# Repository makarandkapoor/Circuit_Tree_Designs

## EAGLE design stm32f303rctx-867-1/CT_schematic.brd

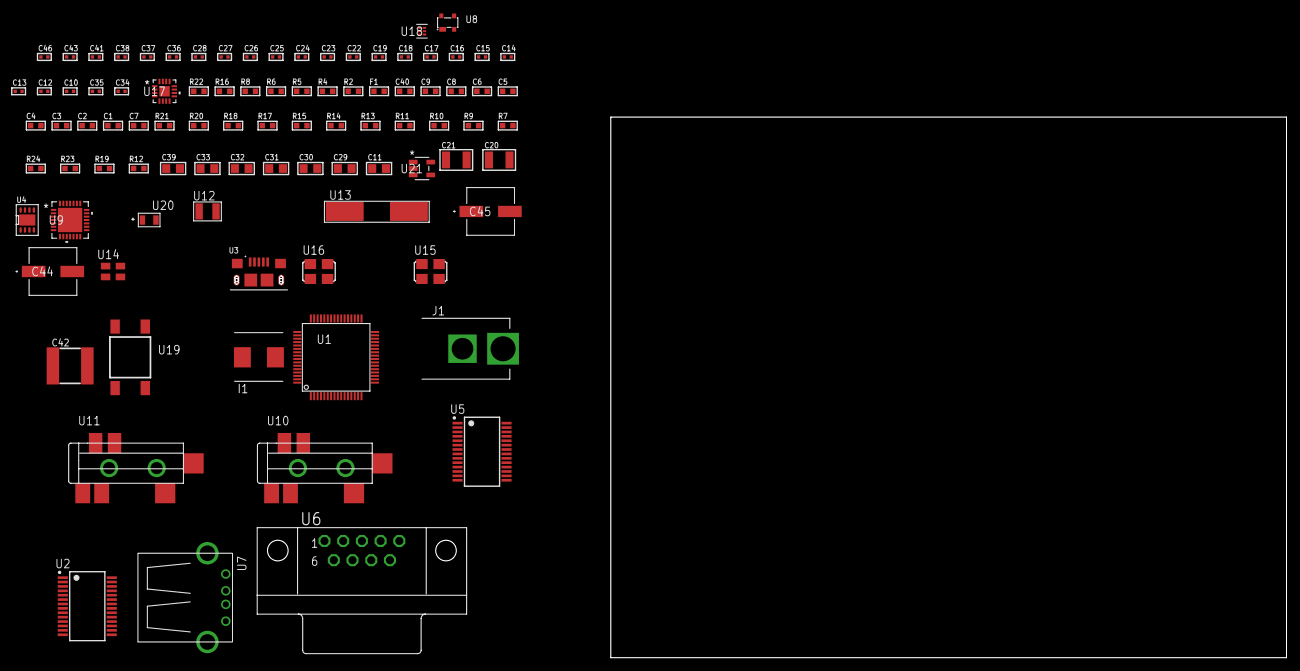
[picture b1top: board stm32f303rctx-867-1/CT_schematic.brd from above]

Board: 2 copper layers, 92 parts (0 on the bottom side), 59 nets, no tracks yet.

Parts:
C1, C9, C40: 1e-06; C0603
C2, C3, C4, C5, C6: 1e-07; C0603
C7: 4.7e-06; C0603
C8: 1e-08; C0603
C10, C12, C13, C14, C15, C16, C17, C18, C19, C24, C25, C26, C27, C28, C41, C43: 1e-07; C0402
C11: 4.7e-06; C0805
C20, C21: 2.2e-05; C1210
C22, C23: 1e-09; C0402
C29, C30, C31, C32, C33, C39: 1e-05; C0805
C34, C35: 2.2e-11; C0402
C36, C37, C38, C46: 1e-08; C0402
C42: 6.8e-05; 2220
C44, C45: 0.0001; EXV-9H
F1: 240.0; L0603
I1: 3.3e-06; WE-HCI_7030/7040/7050
J1: PJ-037B; PJ-037B_PACKAGE
R2: 1000.0; R0603
R4, R8: 4700.0; R0603
R5, R6: 2200.0; R0603
R7, R9, R10, R11, R20, R21: 10000.0; R0603
R12: 100000.0; R0603
R13, R14, R15: 47000.0; R0603
R16: 680.0; R0603
R17: 20000.0; R0603
R18: 91000.0; R0603
R19: 300000.0; R0603
R22: 9100.0; R0603
R23: 680000.0; R0603
R24: 120000.0; R0603
U1: STM32F303RCT6; LQFP64
U2: FT232RL-REEL; SSOP-28
U3: 10118193-0001LF; FCI_10118193-0001LF
U4: PCF85063TP/1Z; SON-8
U5: ST3241EBPR; SSOP-28
U6: 182-009-113R531; 182-009-MALE
U7: 61400416021; USB-A-H
U8: prtr5v0u2ax; SOT143B
U9: WM8731CLSEFL; QFN-28
U10, U11: SJ-43515TS-SMT-TR
U12: ABS07-32.768KHZ-7-T
U13: ABLS-12.288MHZ-B4-T
U14: ASEK-32.768KHz-ECST; ASEK
U15: ASFL1-12MHZ-NCS; ASFL1
U16: ASFL1-25MHZ-NCS; ASFL1
U17: LTC3601EUD#PBF; QFN-16_EP
U18: TPS3895ADRYR; SON-6
U19: 4-1437565-2; SW_4-1437565-2
U20: Q65110A2395; LGM67K-G1J2-24-Z
U21: nc7sz125m5x; NC7SZ125M5X

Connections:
CLK_CRYSTAL_U4_1: U4.1, U12.1
CLK_CRYSTAL_U4_2: U4.2, U12.2
CLK_CRYSTAL_U9_1: C34.1, U9.1, U13.1
CLK_CRYSTAL_U9_2: C35.1, U9.2, U13.2
CLK_U1_3: U1.3, U14.3
CLK_U1_5: U1.5, U16.3
CLK_U2_27: U2.27, U15.3
GND: C1.2, C2.2, C3.2, C4.2, C5.2, C6.2, C7.2, C8.2, C9.2, C10.2, C11.2, C12.2, C13.2, C14.2, C15.2, C18.2, C19.2, C23.2, C24.2, C25.2, C26.2, C27.2, C28.2, C29.2, C30.2, C31.2, C32.2, C33.2, C34.2, C35.2, C36.2, C37.2, C38.2, C39.2, C40.2, C42.1, C42.2, C43.2, C44.2, C45.2, C46.2, J1.2, R2.2, R7.2, R10.2, R13.2, R14.2, R15.2, R17.2, R19.2, R22.2, R24.2, U1.12, U1.31, U1.47, U1.63, U2.7, U2.18, U2.21, U2.25, U2.26, U3.5, U3.6, U3.7, U3.8, U3.9, U4.4, U4.PAD, U5.23, U5.25, U6.5, U7.4, U7.5, U7.6, U8.1, U9.4, U9.15, U9.19, U9.25, U9.26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
NET_U1_7: R4.1, U1.7, U21.4
NET_U1_13: C8.1, C9.1, F1.1, U1.13
NET_U1_49: R6.1, U1.49, U4.5
NET_U1_50: R5.1, U1.50, U4.6
NET_U1_60: R7.1, U1.60
NET_U1_62: U19.3, U19.4
NET_U2_14: R9.1, U2.14
NET_U2_17: C12.1, U2.17
NET_U2_19: R10.1, U2.19
NET_U3_1: R8.1, U3.1
NET_U3_2: U2.16, U3.2
NET_U3_3: U2.15, U3.3
NET_U4_3: R11.1, U4.3
NET_U5_1: C17.1, U5.1
NET_U5_2: C17.2, U5.2
NET_U5_3: C19.1, U5.3
NET_U5_22: R12.1, U5.22
NET_U5_24: C16.2, U5.24
NET_U5_27: C18.1, U5.27
NET_U5_28: C16.1, U5.28
NET_U6_2: U5.4, U6.2
NET_U6_3: U5.9, U6.3
NET_U6_7: U5.5, U6.7
NET_U6_8: U5.10, U6.8
NET_U8_4: U7.1, U8.4
NET_U9_20: C28.1, C33.1, U9.20
NET_U10_2: C21.1, R14.1, U10.2
NET_U10_5: C20.1, R13.1, U10.5
NET_U11_5: C22.1, C23.1, R15.1, R16.1, U11.5
NET_U17_3: C41.2, I1.1, U17.3, U17.4
NET_U17_6: C41.1, U17.6
NET_U17_7: C40.1, U17.7, U17.12
NET_U17_10: R19.1, U17.10
NET_U17_11: R17.1, R18.1, U17.11
NET_U17_ATNET_3: I1.2, R18.2
NET_U18_1: R21.1, R22.1, U18.1
NET_U18_3: R23.2, R24.1, U18.3
NET_U18_4: R20.1, U18.4, U21.2
NET_U19_1: R2.1, U19.1, U19.2
PROC_I2S2_CK: U1.34, U9.7
PROC_I2S2_EXT_SD: U1.35, U9.10
PROC_I2S2_SD: U1.36, U9.8
PROC_I2S2_WS: U1.33, U9.9, U9.11
PROC_UART4_RX: U1.52, U2.1
PROC_UART4_TX: U1.51, U2.5
PROC_UART5_RX: U1.54, U5.19
PROC_UART5_TX: U1.53, U5.14
PROC_USB_DM: U1.44, U7.2, U8.3
PROC_USB_DP: U1.45, U7.3, U8.2
VCC_S1_4V9: C39.1, C44.1, C45.1, J1.1, U17.15, U17.16
VCC_TIER1_3V3: C1.1, C2.1, C3.1, C4.1, C5.1, C6.1, C7.1, C10.1, C11.1, C13.1, C14.1, C15.1, C24.1, C25.1, C26.1, C27.1, C29.1, C30.1, C31.1, C32.1, C36.1, C37.1, C38.1, C42.2, C43.1, C46.1, F1.2, I1.2, R4.2, R5.2, R6.2, R9.2, R11.2, R12.2, R18.2, R20.2, R21.2, R23.1, U1.1, U1.19, U1.32, U1.48, U1.64, U2.4, U2.20, U4.8, U5.26, U9.3, U9.5, U9.12, U9.18, U14.4, U15.4, U16.4, U17.8, U18.6, U21.5

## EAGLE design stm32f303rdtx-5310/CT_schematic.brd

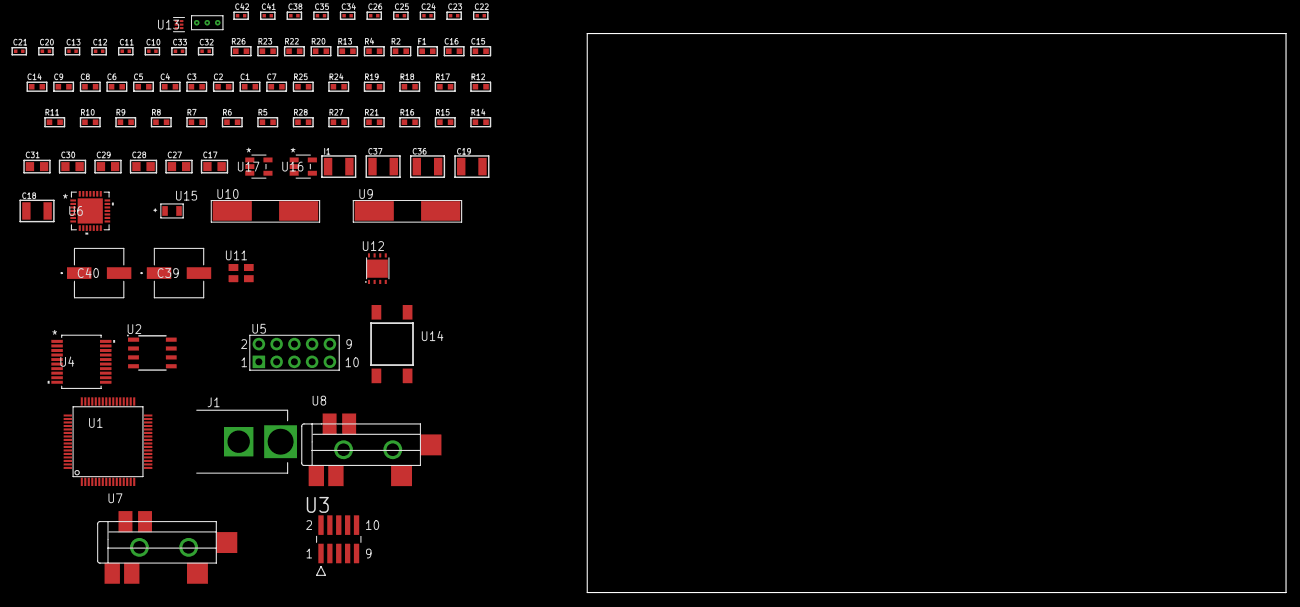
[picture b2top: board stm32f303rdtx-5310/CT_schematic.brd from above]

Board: 2 copper layers, 100.0 x 80.0 mm, 89 parts (0 on the bottom side), 55 nets, no tracks yet.

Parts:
C1, C9, C14, C15, C16: 1e-06; C0603
C2, C3, C4, C5, C6: 1e-07; C0603
C7: 4.7e-06; C0603
C8: 1e-08; C0603
C10, C11: 1e-11; C0402
C12, C34, C35, C41, C42: 1e-08; C0402
C13, C22, C23, C24, C25, C26, C38: 1e-07; C0402
C17: 4.7e-06; C0805
C18, C19: 2.2e-05; C1210
C20, C21: 1e-09; C0402
C27, C28, C29, C30, C31: 1e-05; C0805
C32, C33: 2.2e-11; C0402
C36, C37: 1e-05; C1210
C39, C40: 0.0001; EXV-9H
F1: 240.0; L0603
I1: 1.5e-05; L1210
J1: PJ-037B; PJ-037B_PACKAGE
R2, R23: 1000.0; R0603
R4: 4700.0; R0603
R5, R6, R7, R8, R9, R10, R11, R12, R24, R25: 10000.0; R0603
R13: 5.0; R0603
R14, R15, R16, R21: 100000.0; R0603
R17, R18, R19: 47000.0; R0603
R20: 680.0; R0603
R22: 2231.0; R0603
R26: 9100.0; R0603
R27: 680000.0; R0603
R28: 120000.0; R0603
U1: STM32F303RDT6; LQFP64
U2: AT25010B-SSHL-T; SOIC-8
U3: FTSH-105-01-L-DV-K; SAMTEC_FTSH-105-01-L-DV-K
U4: MAX3218EAP+T; SSOP-20
U5: HTSS-105-01-G-D
U6: WM8731CLSEFL; QFN-28
U7, U8: SJ-43515TS-SMT-TR
U9: ABLS-25.000MHZ-B2F-T
U10: ABLS-12.288MHZ-B4-T
U11: ASEK-32.768KHz-ECST; ASEK
U12: LP3878SDX-ADJ/NOPB; WSON-8
U13: TPS3895ADRYR; SON-6
U14: 4-1437565-2; SW_4-1437565-2
U15: Q65110A2395; LGM67K-G1J2-24-Z
U16, U17: nc7sz125m5x; NC7SZ125M5X
U18: Dummy; DUMMY_PACKAGE_186

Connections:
CLK_CRYSTAL_U1_5: C10.1, U1.5, U9.1
CLK_CRYSTAL_U1_6: C11.1, U1.6, U9.2
CLK_CRYSTAL_U6_1: C32.1, U6.1, U10.1
CLK_CRYSTAL_U6_2: C33.1, U6.2, U10.2
CLK_U1_3: U1.3, U11.3
GND: C1.2, C2.2, C3.2, C4.2, C5.2, C6.2, C7.2, C8.2, C9.2, C10.2, C11.2, C12.2, C13.2, C14.2, C15.2, C16.2, C21.2, C22.2, C23.2, C24.2, C25.2, C26.2, C27.2, C28.2, C29.2, C30.2, C31.2, C32.2, C33.2, C34.2, C35.2, C36.2, C37.2, C38.2, C39.2, C40.2, C41.2, C42.2, J1.2, R2.2, R5.2, R12.2, R13.2, R17.2, R18.2, R19.2, R23.2, R26.2, R28.2, U1.12, U1.18, U1.31, U1.47, U1.63, U2.4, U3.3, U3.5, U4.5, U4.17, U4.20, U5.9, U6.4, U6.15, U6.19, U6.25, U6.26, U6.29, U7.1, U8.1, U11.2, U12.3, U12.PAD, U13.2, U15.C, U16.2, U16.3, U17.1, U17.3, U18.1
NET_U1_7: R4.1, U1.7, U17.4
NET_U1_13: C8.1, C9.1, F1.1, U1.13
NET_U1_60: R5.1, U1.60
NET_U1_62: U14.3, U14.4
NET_U2_3: R6.1, U2.3
NET_U2_7: R8.1, U2.7
NET_U3_9: R13.1, U3.9
NET_U4_1: I1.1, U4.1
NET_U4_2: R14.1, U4.2
NET_U4_3: R15.1, U4.3
NET_U4_4: R16.1, U4.4
NET_U4_15: C16.1, U4.15
NET_U4_16: C17.2, U4.16
NET_U4_18: C17.1, U4.18
NET_U4_19: C15.1, U4.19
NET_U5_3: U4.12, U5.3
NET_U5_4: U4.11, U5.4
NET_U5_5: U4.14, U5.5
NET_U5_6: U4.13, U5.6
NET_U6_20: C26.1, C31.1, U6.20
NET_U7_2: C19.1, R18.1, U7.2
NET_U7_5: C18.1, R17.1, U7.5
NET_U8_5: C20.1, C21.1, R19.1, R20.1, U8.5
NET_U12_1: C35.1, U12.1
NET_U12_6: R22.2, R23.1, U12.6
NET_U12_8: R21.1, U12.8
NET_U13_1: R25.1, R26.1, U13.1
NET_U13_3: R27.2, R28.1, U13.3
NET_U13_4: R24.1, U13.4, U16.4, U17.2
NET_U14_1: R2.1, U14.1, U14.2
PROC_ADC1_IN1: U1.14, U18.3
PROC_ADC1_IN2: U1.15, U18.2
PROC_I2S2_CK: U1.34, U6.7
PROC_I2S2_EXT_SD: U1.35, U6.10
PROC_I2S2_SD: U1.36, U6.8
PROC_I2S2_WS: U1.33, U6.9, U6.11
PROC_SPI1_MISO: U1.22, U2.2
PROC_SPI1_MOSI: U1.23, U2.5
PROC_SPI1_NSS: R7.1, U1.20, U2.1
PROC_SPI1_SCK: U1.21, U2.6
PROC_SYS_JTCK_SWCLK: R12.1, U1.49, U3.4
PROC_SYS_JTDI: R10.1, U1.50, U3.8
PROC_SYS_JTDO_TRACESWO: U1.55, U3.6
PROC_SYS_JTMS_SWDIO: R11.1, U1.46, U3.2
PROC_UART4_RX: U1.52, U4.9
PROC_UART4_TX: U1.51, U4.7
RST_OUT_U3_JTAG_RST_B: R9.1, U3.10, U16.1
VCC_S1_15V0: C36.1, C39.1, C40.1, J1.1, R21.2, U12.4
VCC_TIER1_3V3: C1.1, C2.1, C3.1, C4.1, C5.1, C6.1, C7.1, C12.1, C13.1, C14.1, C22.1, C23.1, C24.1, C25.1, C27.1, C28.1, C29.1, C30.1, C34.1, C37.1, C38.1, C41.1, C42.1, F1.2, I1.2, R4.2, R6.2, R7.2, R8.2, R9.2, R10.2, R11.2, R14.2, R15.2, R16.2, R22.1, R24.2, R25.2, R27.1, U1.1, U1.19, U1.32, U1.48, U1.64, U2.8, U3.1, U4.6, U6.3, U6.5, U6.12, U6.18, U11.4, U12.5, U13.6, U16.5, U17.5

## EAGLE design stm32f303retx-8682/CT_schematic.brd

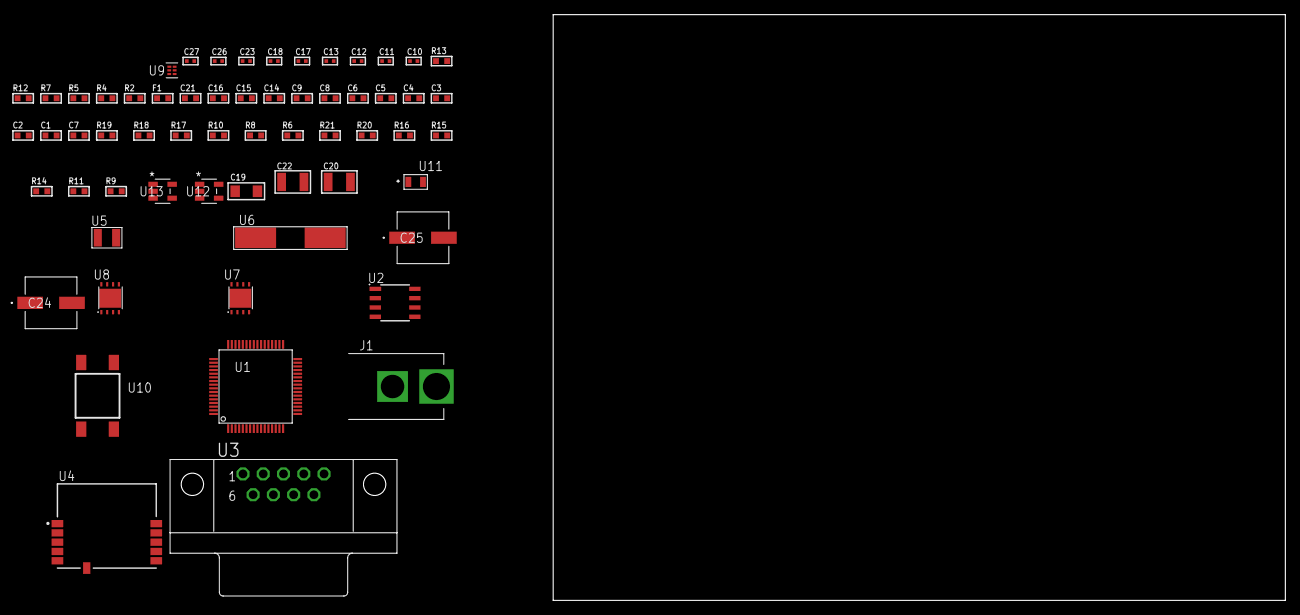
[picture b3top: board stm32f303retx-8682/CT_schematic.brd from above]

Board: 2 copper layers, 100.0 x 80.0 mm, 61 parts (0 on the bottom side), 32 nets, no tracks yet.

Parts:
C1, C9, C14, C15, C16, C21: 1e-06; C0603
C2, C3, C4, C5, C6: 1e-07; C0603
C7: 4.7e-06; C0603
C8: 1e-08; C0603
C10, C11, C12, C13: 1e-11; C0402
C17, C23: 1e-07; C0402
C18, C26, C27: 1e-08; C0402
C19: 1e-05; C1206
C20, C22: 1e-05; C1210
C24, C25: 0.0001; EXV-9H
F1: 240.0; L0603
J1: PJ-037B; PJ-037B_PACKAGE
R2, R13: 1000.0; R0603
R4, R5: 4700.0; R0603
R6, R8, R17, R18: 10000.0; R0603
R7: 120.0; R0603
R9, R11, R14, R16: 100000.0; R0603
R10: 47000.0; R0603
R12: 1500.0; R0603
R15: 300000.0; R0603
R19: 18000.0; R0603
R20: 470000.0; R0603
R21: 120000.0; R0603
U1: STM32F303RET7; LQFP64
U2: MCP2562-E/SN; SOIC-8
U3: 182-009-113R531; 182-009-MALE
U4: SPBTLE-RF; XCVR_SPBTLE-RF
U5: ABS07-32.768KHZ-7-T
U6: ABLS-25.000MHZ-B2F-T
U7: LP3878SDX-ADJ/NOPB; WSON-8
U8: LP2951ACSDX/NOPB; WSON-8
U9: TPS3895ADRYR; SON-6
U10: 4-1437565-2; SW_4-1437565-2
U11: Q65110A2395; LGM67K-G1J2-24-Z
U12, U13: nc7sz125m5x; NC7SZ125M5X

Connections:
CLK_CRYSTAL_U1_3: C10.1, U1.3, U5.1
CLK_CRYSTAL_U1_4: C11.1, U1.4, U5.2
CLK_CRYSTAL_U1_5: C12.1, U1.5, U6.1
CLK_CRYSTAL_U1_6: C13.1, U1.6, U6.2
GND: C1.2, C2.2, C3.2, C4.2, C5.2, C6.2, C7.2, C8.2, C9.2, C10.2, C11.2, C12.2, C13.2, C14.2, C15.2, C16.2, C17.2, C18.2, C19.2, C20.2, C21.2, C22.2, C23.2, C24.2, C25.2, C26.2, C27.2, J1.2, R2.2, R6.2, R9.2, R10.2, R13.2, R16.2, R19.2, R21.2, U1.12, U1.18, U1.31, U1.47, U1.63, U2.2, U2.8, U3.5, U4.6, U7.3, U7.PAD, U8.3, U8.4, U8.PAD, U9.2, U11.C, U12.1, U12.3, U13.1, U13.3
NET_U1_7: R5.1, U1.7, U13.4
NET_U1_13: C8.1, C9.1, F1.1, U1.13
NET_U1_60: R6.1, U1.60
NET_U1_62: U10.3, U10.4
NET_U2_6: R7.2, U2.6
NET_U3_2: R7.2, U2.6, U3.2
NET_U3_3: R7.1, U2.7, U3.3
NET_U4_11: R4.1, U4.11, U12.4
NET_U7_1: C18.1, U7.1
NET_U7_6: R12.2, R13.1, U7.6
NET_U7_8: R11.1, U7.8
NET_U8_5: R14.1, U8.5
NET_U8_7: R15.2, R16.1, U8.7
NET_U9_1: R18.1, R19.1, U9.1
NET_U9_3: R20.2, R21.1, U9.3
NET_U9_4: R17.1, U9.4, U12.2, U13.2
NET_U10_1: R2.1, U10.1, U10.2
PROC_CAN_RX: U1.44, U2.4
PROC_CAN_TX: U1.45, U2.1
PROC_GPIO_TO_U4_SPI_IRQ: R10.1, U1.2, U4.4
PROC_SPI1_MISO: U1.22, U4.8
PROC_SPI1_MOSI: U1.23, U4.9
PROC_SPI1_NSS: R8.1, U1.20, U4.10
PROC_SPI1_SCK: R9.1, U1.21, U4.7
VCC_S1_8V6: C19.1, C21.1, C24.1, C25.1, J1.1, R11.2, U7.4, U8.8
VCC_TIER1_2V5: C1.1, C2.1, C3.1, C4.1, C5.1, C6.1, C7.1, C15.1, C16.1, C17.1, C20.1, C23.1, C26.1, C27.1, F1.2, R4.2, R5.2, R8.2, R12.1, R17.2, R18.2, R20.1, U1.1, U1.19, U1.32, U1.48, U1.64, U2.5, U4.5, U7.5, U9.6, U12.5, U13.5
VCC_TIER1_5V0: C14.1, C22.1, R14.2, R15.1, U2.3, U8.1

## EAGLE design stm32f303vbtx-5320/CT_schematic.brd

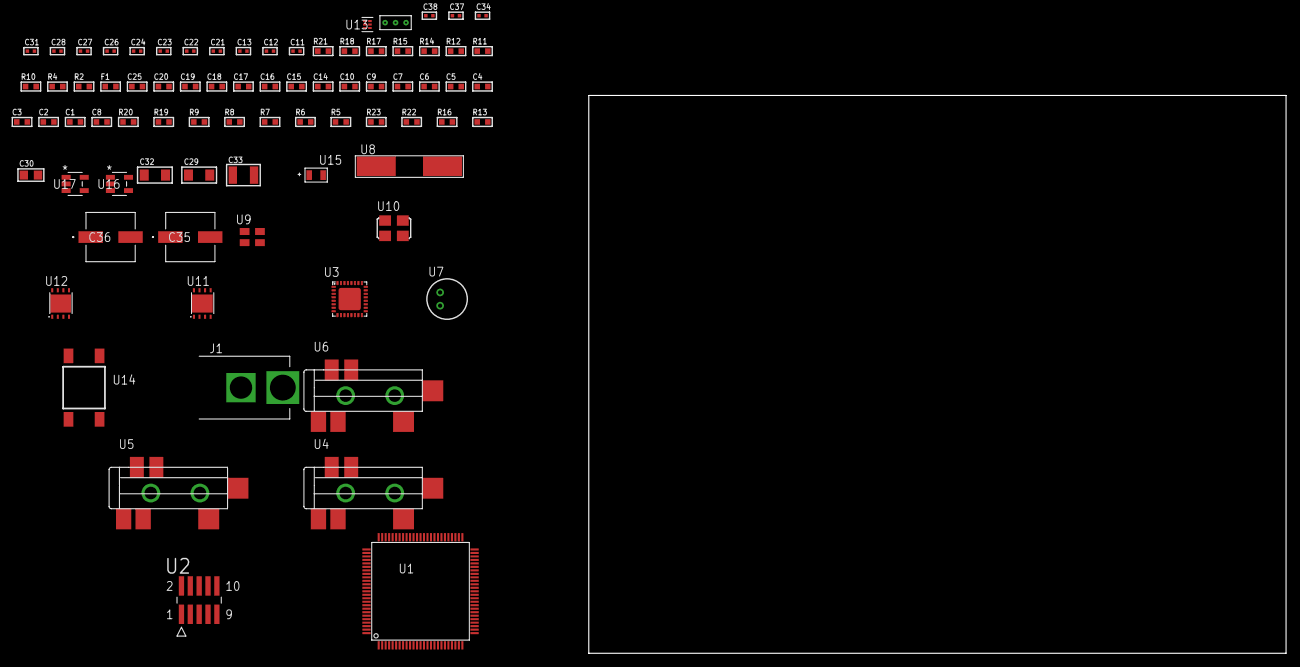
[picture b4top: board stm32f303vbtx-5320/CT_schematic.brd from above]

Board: 2 copper layers, 100.0 x 80.0 mm, 79 parts (0 on the bottom side), 47 nets, no tracks yet.

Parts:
C1, C10, C14, C15, C16, C17, C18, C19, C20, C25: 1e-06; C0603
C2, C3, C4, C5, C6, C7: 1e-07; C0603
C8: 4.7e-06; C0603
C9: 1e-08; C0603
C11, C12: 1e-11; C0402
C13, C21, C22, C23, C24, C34: 1e-07; C0402
C26, C27, C28, C31, C37, C38: 1e-08; C0402
C29, C32: 1e-05; C1206
C30: 1e-05; C0805
C33: 1e-05; C1210
C35, C36: 0.0001; EXV-9H
F1: 240.0; L0603
J1: PJ-037B; PJ-037B_PACKAGE
R2, R15, R18: 1000.0; R0603
R4: 4700.0; R0603
R5, R6, R7, R8, R9, R19, R20: 10000.0; R0603
R10: 5.0; R0603
R11, R12: 1270.0; R0603
R13, R16: 100000.0; R0603
R14: 200.0; R0603
R17: 2231.0; R0603
R21: 9100.0; R0603
R22: 680000.0; R0603
R23: 120000.0; R0603
U1: STM32F303VBT6; LQFP100
U2: FTSH-105-01-L-DV-K; SAMTEC_FTSH-105-01-L-DV-K
U3: SGTL5000XNAA3; QFN-32
U4, U5, U6: SJ-43515TS-SMT-TR
U7: WM-64PCT; WM-64PC
U8: ABLS-25.000MHZ-B2F-T
U9: ASEK-32.768KHz-ECST; ASEK
U10: ASFL-24.57MHZ-NCS; ASFL1
U11, U12: LP3878SDX-ADJ/NOPB; WSON-8
U13: TPS3895ADRYR; SON-6
U14: 4-1437565-2; SW_4-1437565-2
U15: Q65110A2395; LGM67K-G1J2-24-Z
U16, U17: nc7sz125m5x; NC7SZ125M5X
U18: Dummy; DUMMY_PACKAGE_164

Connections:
CLK_CRYSTAL_U1_12: C11.1, U1.12, U8.1
CLK_CRYSTAL_U1_13: C12.1, U1.13, U8.2
CLK_U1_8: U1.8, U9.3
CLK_U3_21: U3.21, U10.3
GND: C1.2, C2.2, C3.2, C4.2, C5.2, C6.2, C7.2, C8.2, C9.2, C10.2, C11.2, C12.2, C13.2, C21.2, C22.2, C23.2, C24.2, C25.2, C26.2, C27.2, C28.2, C29.2, C30.2, C31.2, C32.2, C33.2, C34.2, C35.2, C36.2, C37.2, C38.2, J1.2, R2.2, R5.2, R9.2, R10.2, R12.2, R15.2, R18.2, R21.2, R23.2, U1.20, U1.49, U1.74, U1.99, U2.3, U2.5, U3.1, U3.3, U3.7, U3.EXP, U5.1, U6.1, U7.2, U9.2, U10.2, U11.3, U11.PAD, U12.3, U12.PAD, U13.2, U15.C, U16.2, U16.3, U17.1, U17.3, U18.1
NET_U1_14: R4.1, U1.14, U17.4
NET_U1_22: C9.1, C10.1, F1.1, U1.21, U1.22
NET_U1_94: R5.1, U1.94
NET_U1_98: U14.3, U14.4
NET_U2_9: R10.1, U2.9
NET_U3_10: C24.1, U3.10
NET_U3_29: R11.1, U3.29
NET_U3_31: R12.1, U3.31
NET_U4_1: U3.4, U4.1
NET_U4_2: U3.2, U4.2
NET_U4_5: U3.6, U4.5
NET_U5_2: C15.1, U5.2
NET_U5_5: C14.1, U5.5
NET_U6_2: C17.1, C18.1, U6.2
NET_U6_5: C16.1, U6.5
NET_U6_13: C17.2, C18.2
NET_U7_1: C19.1, C20.1, C25.1, U3.16, U7.1
NET_U7_15: C19.2, C20.2
NET_U11_1: C28.1, U11.1
NET_U11_6: R14.2, R15.1, U11.6
NET_U11_8: R13.1, U11.8
NET_U12_1: C31.1, U12.1
NET_U12_6: R17.2, R18.1, U12.6
NET_U12_8: R16.1, U12.8
NET_U13_1: R20.1, R21.1, U13.1
NET_U13_3: R22.2, R23.1, U13.3
NET_U13_4: R19.1, U13.4, U16.4, U17.2
NET_U14_1: R2.1, U14.1, U14.2
PROC_I2S2_CK: U1.52, U3.24
PROC_I2S2_EXT_SD: U1.53, U3.25
PROC_I2S2_SD: U1.54, U3.26
PROC_I2S2_WS: U1.51, U3.23
PROC_PE2: U1.1, U18.2
PROC_PE3: U1.2, U18.3
PROC_SYS_JTCK_SWCLK: R9.1, U1.76, U2.4
PROC_SYS_JTDI: R7.1, U1.77, U2.8
PROC_SYS_JTDO_TRACESWO: U1.89, U2.6
PROC_SYS_JTMS_SWDIO: R8.1, U1.72, U2.2
RST_OUT_U2_JTAG_RST_B: R6.1, U2.10, U16.1
VCC_S1_5V3: C29.1, C32.1, C35.1, C36.1, J1.1, R13.2, R16.2, U11.4, U12.4
VCC_TIER1_1V2: C21.1, C30.1, R14.1, U3.30, U11.5
VCC_TIER1_3V3: C1.1, C2.1, C3.1, C4.1, C5.1, C6.1, C7.1, C8.1, C13.1, C22.1, C23.1, C26.1, C27.1, C33.1, C34.1, C37.1, C38.1, F1.2, R4.2, R6.2, R7.2, R8.2, R11.2, R17.1, R19.2, R20.2, R22.1, U1.6, U1.28, U1.50, U1.75, U1.100, U2.1, U3.5, U3.20, U9.4, U10.4, U12.5, U13.6, U16.5, U17.5

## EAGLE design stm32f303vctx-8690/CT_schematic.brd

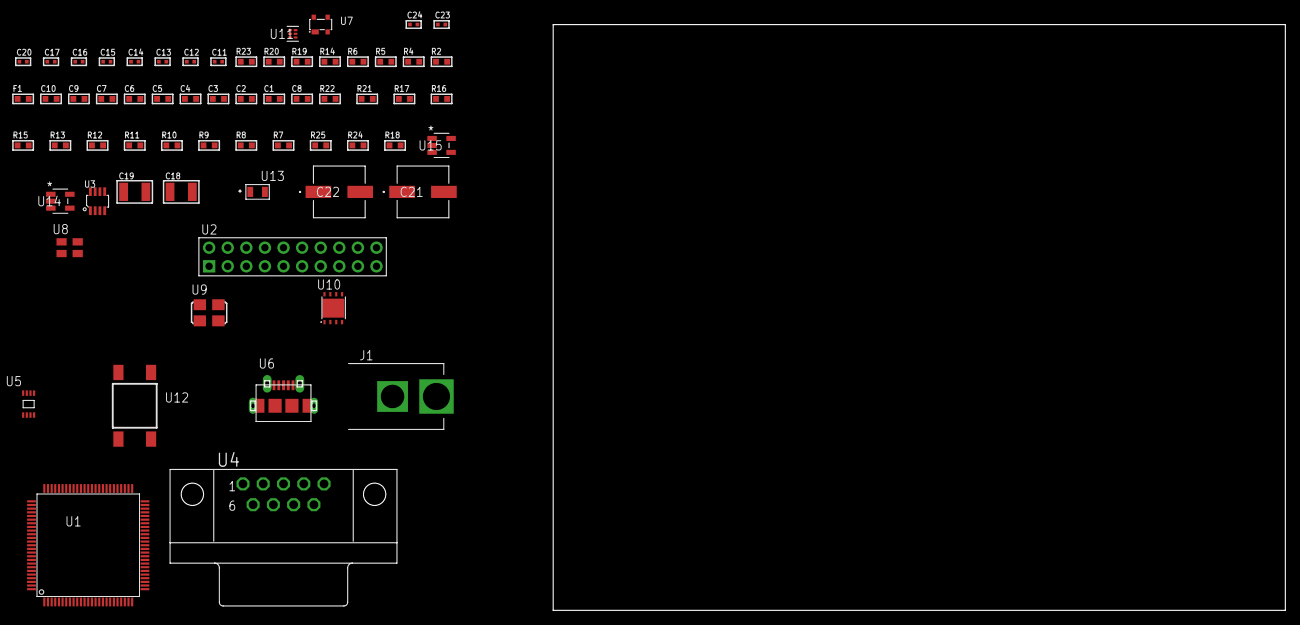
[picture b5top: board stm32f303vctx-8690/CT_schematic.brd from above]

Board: 2 copper layers, 64 parts (0 on the bottom side), 36 nets, no tracks yet.

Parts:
C1, C10: 1e-06; C0603
C2, C3, C4, C5, C6, C7: 1e-07; C0603
C8: 4.7e-06; C0603
C9: 1e-08; C0603
C11, C12, C13, C20: 1e-07; C0402
C14, C15, C16, C17, C23, C24: 1e-08; C0402
C18, C19: 1e-05; C1210
C21, C22: 0.0001; EXV-9H
F1: 240.0; L0603
J1: PJ-037B; PJ-037B_PACKAGE
R2, R20: 1000.0; R0603
R4: 4700.0; R0603
R5, R6: 2200.0; R0603
R7, R8, R9, R10, R11, R12, R13, R15, R16, R17, R21, R22: 10000.0; R0603
R14: 120.0; R0603
R18: 100000.0; R0603
R19: 2231.0; R0603
R23: 9100.0; R0603
R24: 680000.0; R0603
R25: 120000.0; R0603
U1: STM32F303VCT7; LQFP100
U2: TST-110-05-T-D-RA
U3: MAX3051EKA+T; SOT-23-8
U4: 182-009-113R531; 182-009-MALE
U5: 24AA64T-I/MNY; TDFN-8/6MM
U6: 47590-0001; MICRO_USB_AB
U7: prtr5v0u2ax; SOT143B
U8: ASEK-32.768KHz-ECST; ASEK
U9: ASFL1-25MHZ-NCS; ASFL1
U10: LP3878SDX-ADJ/NOPB; WSON-8
U11: TPS3895ADRYR; SON-6
U12: 4-1437565-2; SW_4-1437565-2
U13: Q65110A2395; LGM67K-G1J2-24-Z
U14, U15: nc7sz125m5x; NC7SZ125M5X

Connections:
CLK_U1_8: U1.8, U8.3
CLK_U1_12: U1.12, U9.3
GND: C1.2, C2.2, C3.2, C4.2, C5.2, C6.2, C7.2, C8.2, C9.2, C10.2, C11.2, C12.2, C13.2, C14.2, C15.2, C16.2, C17.2, C18.2, C19.2, C20.2, C21.2, C22.2, C23.2, C24.2, J1.2, R2.2, R7.2, R13.2, R16.2, R17.2, R20.2, R23.2, R25.2, U1.20, U1.49, U1.74, U1.99, U2.4, U2.6, U2.8, U2.10, U2.12, U2.14, U2.16, U2.18, U2.20, U3.2, U3.8, U4.5, U5.4, U5.7, U6.5, U6.6, U6.7, U6.8, U6.9, U7.1, U8.2, U9.2, U10.3, U10.PAD, U11.2, U13.C, U14.2, U14.3, U15.1, U15.3
NET_U1_14: R4.1, U1.14, U15.4
NET_U1_22: C9.1, C10.1, F1.1, U1.21, U1.22
NET_U1_92: R5.1, U1.92, U5.6
NET_U1_93: R6.1, U1.93, U5.5
NET_U1_94: R7.1, U1.94
NET_U1_98: U12.3, U12.4
NET_U2_19: R13.1, U2.19
NET_U3_6: R14.2, U3.6
NET_U4_2: R14.2, U3.6, U4.2
NET_U4_3: R14.1, U3.7, U4.3
NET_U5_1: R15.1, U5.1
NET_U5_2: R16.1, U5.2
NET_U5_3: R17.1, U5.3
NET_U7_4: U6.1, U7.4
NET_U10_1: C17.1, U10.1
NET_U10_6: R19.2, R20.1, U10.6
NET_U10_8: R18.1, U10.8
NET_U11_1: R22.1, R23.1, U11.1
NET_U11_3: R24.2, R25.1, U11.3
NET_U11_4: R21.1, U11.4, U14.4, U15.2
NET_U12_1: R2.1, U12.1, U12.2
PROC_CAN_RX: U1.81, U3.4
PROC_CAN_TX: U1.82, U3.1
PROC_SYS_JTCK_SWCLK: R11.1, U1.76, U2.9
PROC_SYS_JTDI: R9.1, U1.77, U2.5
PROC_SYS_JTDO_TRACESWO: U1.89, U2.13
PROC_SYS_JTMS_SWDIO: R10.1, U1.72, U2.7
PROC_SYS_NJTRST: R8.1, U1.90, U2.3
PROC_USB_DM: U1.70, U6.2, U7.3
PROC_USB_DP: U1.71, U6.3, U7.2
RST_OUT_U2_SRESET_B: R12.1, U2.15, U14.1
VCC_S1_12V1: C18.1, C21.1, C22.1, J1.1, R18.2, U10.4
VCC_TIER1_3V3: C1.1, C2.1, C3.1, C4.1, C5.1, C6.1, C7.1, C8.1, C11.1, C12.1, C13.1, C14.1, C15.1, C16.1, C19.1, C20.1, C23.1, C24.1, F1.2, R4.2, R5.2, R6.2, R8.2, R9.2, R10.2, R11.2, R12.2, R15.2, R19.1, R21.2, R22.2, R24.1, U1.6, U1.28, U1.50, U1.75, U1.100, U2.1, U2.2, U3.3, U5.8, U8.4, U9.4, U10.5, U11.6, U14.5, U15.5

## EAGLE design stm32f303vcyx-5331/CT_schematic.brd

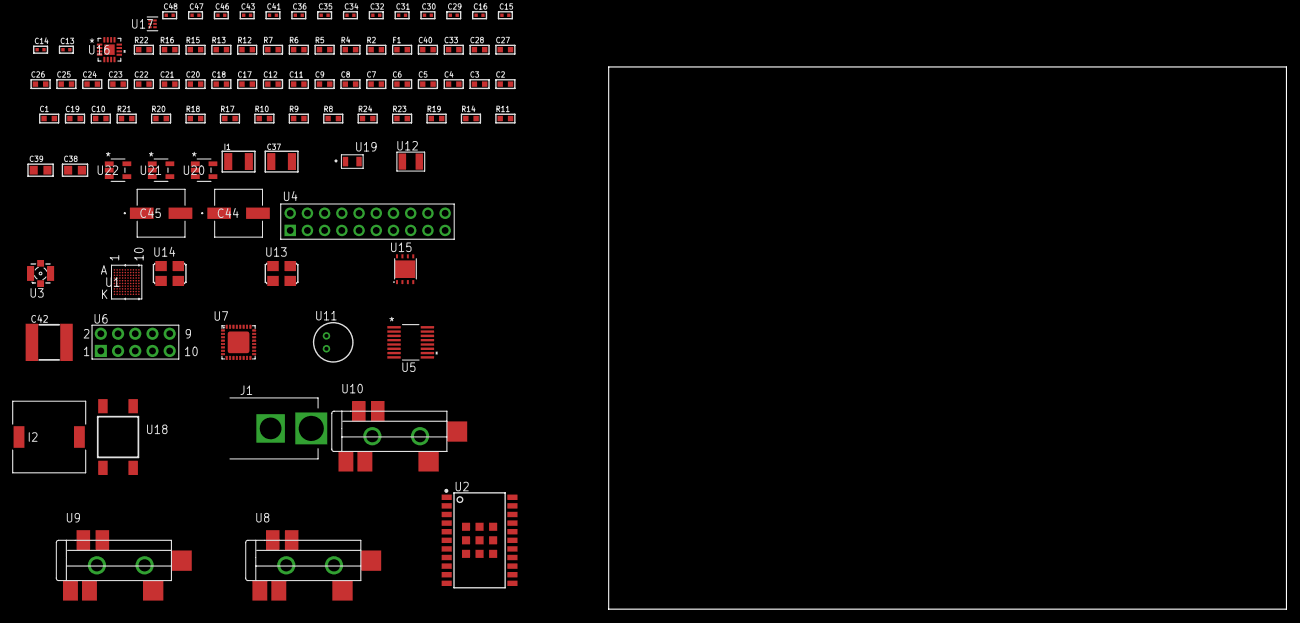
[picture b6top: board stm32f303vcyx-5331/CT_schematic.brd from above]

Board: 2 copper layers, 100.0 x 80.0 mm, 96 parts (0 on the bottom side), 64 nets, no tracks yet.

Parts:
C1, C12, C17, C18, C20, C21, C22, C23, C24, C25, C26, C27, C28, C33, C40: 1e-06; C0603
C2, C3, C4, C5, C6, C7, C8, C9: 1e-07; C0603
C10: 4.7e-06; C0603
C11: 1e-08; C0603
C13, C14: 1e-11; C0402
C15, C16, C29, C30, C31, C32, C41, C43: 1e-07; C0402
C19: 2.2e-07; C0603
C34, C35, C36, C46, C47, C48: 1e-08; C0402
C37: 1e-05; C1210
C38, C39: 1e-05; C0805
C42: 6.8e-05; 2220
C44, C45: 0.0001; EXV-9H
F1: 240.0; L0603
I1: 1e-05; L1210
I2: 7e-06; DR1040
J1: PJ-037B; PJ-037B_PACKAGE
R2, R16: 1000.0; R0603
R4, R5: 4700.0; R0603
R6, R7: 2200.0; R0603
R8, R9, R10, R20, R21: 10000.0; R0603
R11, R14: 100000.0; R0603
R12, R13: 1270.0; R0603
R15: 200.0; R0603
R17: 20000.0; R0603
R18: 91000.0; R0603
R19: 300000.0; R0603
R22: 9100.0; R0603
R23: 680000.0; R0603
R24: 120000.0; R0603
U1: STM32F303VCY6TR; WLCSP100
U2: A2200-A
U3: 73412-0114; COAXIAL_C
U4: TST-110-05-T-D-RA
U5: LTC2804CGN-1#PBF; SSOP-16
U6: HTSS-105-01-G-D
U7: SGTL5000XNAA3; QFN-32
U8, U9, U10: SJ-43515TS-SMT-TR
U11: WM-64PCT; WM-64PC
U12: ABS07-32.768KHZ-7-T
U13: ASFL-24.57MHZ-NCS; ASFL1
U14: ASFL1-25MHZ-NCS; ASFL1
U15: LP3878SDX-ADJ/NOPB; WSON-8
U16: LTC3601EUD#PBF; QFN-16_EP
U17: TPS3895ADRYR; SON-6
U18: 4-1437565-2; SW_4-1437565-2
U19: Q65110A2395; LGM67K-G1J2-24-Z
U20, U21, U22: nc7sz125m5x; NC7SZ125M5X

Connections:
CLK_CRYSTAL_U1_C10: C13.1, U1.C10, U12.1
CLK_CRYSTAL_U1_D9: C14.1, U1.D9, U12.2
CLK_U1_F10: U1.F10, U14.3
CLK_U7_21: U7.21, U13.3
GND: C1.2, C2.2, C3.2, C4.2, C5.2, C6.2, C7.2, C8.2, C9.2, C10.2, C11.2, C12.2, C13.2, C14.2, C15.2, C16.2, C17.2, C18.2, C20.2, C21.2, C29.2, C30.2, C31.2, C32.2, C33.2, C34.2, C35.2, C36.2, C37.2, C38.2, C39.2, C40.2, C42.1, C42.2, C43.2, C44.2, C45.2, C46.2, C47.2, C48.2, J1.2, R2.2, R8.2, R13.2, R16.2, R17.2, R19.2, R22.2, R24.2, U1.A1, U1.A2, U1.B1, U1.C7, U1.H8, U1.J1, U1.K1, U1.K2, U1.K9, U1.K10, U2.7, U2.8, U2.23, U2.24, U2.25, U2.26, U2.27, U2.28, U2.29, U2.30, U2.31, U4.4, U4.6, U4.8, U4.10, U4.12, U4.14, U4.16, U4.18, U4.20, U5.8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
NET_U1_A7: R8.1, U1.A7
NET_U1_B2: R6.1, U1.B2, U2.15
NET_U1_C5: R7.1, U1.C5, U2.16
NET_U1_E9: R5.1, U1.E9, U22.4
NET_U1_J10: C11.1, C12.1, F1.1, U1.J8, U1.J10
NET_U1_K7: U18.3, U18.4
NET_U2_2: R9.2, U2.2
NET_U2_17: R9.1, U2.17
NET_U2_22: R4.1, U2.22, U21.4
NET_U3_1: U2.11, U3.1
NET_U3_2: U2.10, U3.2, U3.3, U3.4
NET_U5_6: C17.1, U5.6
NET_U5_7: C19.1, I1.2, U5.7
NET_U5_9: C18.1, U5.9
NET_U5_10: C19.2, U5.10
NET_U5_11: R11.1, U5.11
NET_U6_3: U5.1, U6.3
NET_U6_4: U5.2, U6.4
NET_U6_5: U5.3, U6.5
NET_U6_6: U5.4, U6.6
NET_U7_10: C32.1, U7.10
NET_U7_29: R12.1, U7.29
NET_U7_31: R13.1, U7.31
NET_U8_1: U7.4, U8.1
NET_U8_2: U7.2, U8.2
NET_U8_5: U7.6, U8.5
NET_U9_2: C23.1, U9.2
NET_U9_5: C22.1, U9.5
NET_U10_2: C25.1, C26.1, U10.2
NET_U10_5: C24.1, U10.5
NET_U10_13: C25.2, C26.2
NET_U11_1: C27.1, C28.1, C33.1, U7.16, U11.1
NET_U11_15: C27.2, C28.2
NET_U15_1: C36.1, U15.1
NET_U15_6: R15.2, R16.1, U15.6
NET_U15_8: R14.1, U15.8
NET_U16_3: C41.2, I2.1, U16.3, U16.4
NET_U16_6: C41.1, U16.6
NET_U16_7: C40.1, U16.7, U16.12
NET_U16_10: R19.1, U16.10
NET_U16_11: R17.1, R18.1, U16.11
NET_U16_ATNET_3: I2.2, R18.2
NET_U17_1: R21.1, R22.1, U17.1
NET_U17_3: R23.2, R24.1, U17.3
NET_U17_4: R20.1, U17.4, U20.4, U21.2, U22.2
NET_U18_1: R2.1, U18.1, U18.2
PROC_I2S2_CK: U1.J3, U7.24
PROC_I2S2_EXT_SD: U1.J2, U7.25
PROC_I2S2_SD: U1.H4, U7.26
PROC_I2S2_WS: U1.J4, U7.23
PROC_SYS_JTCK_SWCLK: U1.C2, U4.9
PROC_SYS_JTDO_TRACESWO: U1.A5, U4.13
PROC_SYS_JTMS_SWDIO: U1.E3, U4.7
PROC_UART4_RX: U1.D3, U5.16
PROC_UART4_TX: U1.E4, U5.14
RST_OUT_U4_SRESET_B: R10.1, U4.15, U20.1
VCC_S1_12V5: C37.1, C39.1, C44.1, C45.1, J1.1, R14.2, U15.4, U16.15, U16.16
VCC_TIER1_1V2: C29.1, C38.1, R15.1, U7.30, U15.5
VCC_TIER1_3V3: C1.1, C2.1, C3.1, C4.1, C5.1, C6.1, C7.1, C8.1, C9.1, C10.1, C15.1, C16.1, C20.1, C21.1, C30.1, C31.1, C34.1, C35.1, C42.2, C43.1, C46.1, C47.1, C48.1, F1.2, I1.1, I2.2, R4.2, R5.2, R6.2, R7.2, R10.2, R11.2, R12.2, R18.2, R20.2, R21.2, R23.1, U1.A9, U1.A10, U1.B8, U1.B10, U1.D2, U1.D8, U1.J5, U1.K8, U2.20, U4.1, U5.5, U5.12, U7.5, U7.20, U13.4, U14.4, U16.8, U17.6, U20.5, U21.5, U22.5

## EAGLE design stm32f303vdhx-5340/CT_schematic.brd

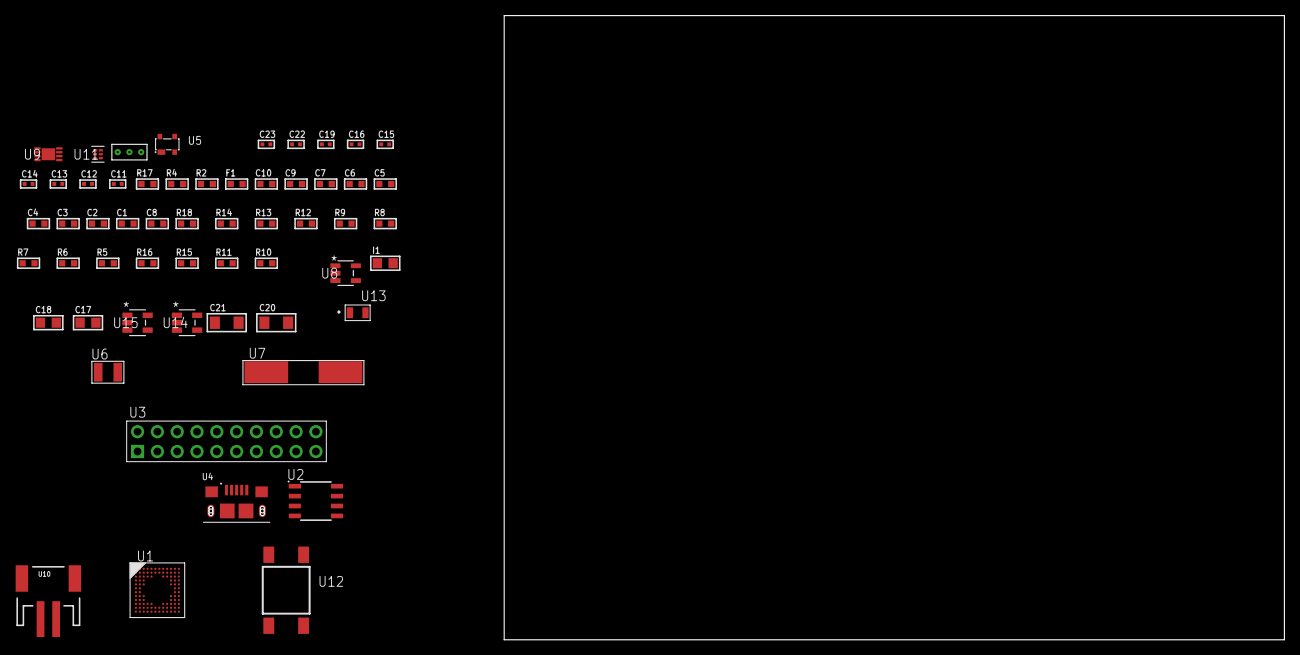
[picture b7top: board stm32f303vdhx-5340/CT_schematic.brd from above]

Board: 2 copper layers, 57 parts (0 on the bottom side), 35 nets, no tracks yet.

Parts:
C1, C10: 1e-06; C0603
C2, C3, C4, C5, C6, C7: 1e-07; C0603
C8: 4.7e-06; C0603
C9: 1e-08; C0603
C11, C12, C13, C14: 1e-11; C0402
C15, C22, C23: 1e-08; C0402
C16, C19: 1e-07; C0402
C17, C18: 1e-05; C0805
C20, C21: 1e-05; C1206
F1: 240.0; L0603
I1: 4.7e-06; L0805
R2: 1000.0; R0603
R4: 4700.0; R0603
R5, R6, R7, R8, R9, R12, R13, R18: 10000.0; R0603
R10: 309473.68421053; R0603
R11: 1000000.0; R0603
R14: 18000.0; R0603
R15: 470000.0; R0603
R16: 120000.0; R0603
R17: 2000.0; R0603
U1: STM32F303VDH6; UFBGA100
U2: AT25640B-SSHL-T; SOIC-8
U3: TST-110-05-T-D-RA
U4: 10118193-0001LF; FCI_10118193-0001LF
U5: prtr5v0u2ax; SOT143B
U6: ABS07-32.768KHZ-7-T
U7: ABLS-25.000MHZ-B2F-T
U8: ltc3406es5; TSOT-23-5
U9: MCP73831T-2ACI/MC; DFN8_2X3MC
U10: S2B-PH-SM4-TB(LF)(SN); JST-2-SMD
U11: TPS3895ADRYR; SON-6
U12: 4-1437565-2; SW_4-1437565-2
U13: Q65110A2395; LGM67K-G1J2-24-Z
U14, U15: nc7sz125m5x; NC7SZ125M5X
U16: Dummy; DUMMY_PACKAGE_122

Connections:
CLK_CRYSTAL_U1_D1: C11.1, U1.D1, U6.1
CLK_CRYSTAL_U1_E1: C12.1, U1.E1, U6.2
CLK_CRYSTAL_U1_F1: C13.1, U1.F1, U7.1
CLK_CRYSTAL_U1_G1: C14.1, U1.G1, U7.2
GND: C1.2, C2.2, C3.2, C4.2, C5.2, C6.2, C7.2, C8.2, C9.2, C10.2, C11.2, C12.2, C13.2, C14.2, C15.2, C16.2, C17.2, C18.1, C18.2, C19.2, C20.2, C21.2, C22.2, C23.2, R2.2, R5.2, R10.2, R14.2, R16.2, R17.2, U1.D3, U1.E3, U1.F11, U1.F12, U1.K1, U2.4, U3.4, U3.6, U3.8, U3.10, U3.12, U3.14, U3.16, U3.18, U3.20, U4.5, U4.6, U4.7, U4.8, U4.9, U5.1, U8.2, U9.6, U9.9, U10.2, U11.2, U13.C, U14.2, U14.3, U15.1, U15.3, U16.1
INPUT_USBPOWER_5V: C20.1, R18.2, U4.1, U5.4, U9.1, U9.2
NET_U1_A4: R5.1, U1.A4
NET_U1_H2: R4.1, U1.H2, U15.4
NET_U1_L1: C9.1, C10.1, F1.1, U1.L1, U1.M1
NET_U1_M12: U12.3, U12.4
NET_U2_3: R6.1, U2.3
NET_U2_7: R8.1, U2.7
NET_U8_3: I1.1, U8.3
NET_U8_5: R10.1, R11.1, U8.5
NET_U8_ATNET_3: I1.2, R11.2
NET_U9_5: R18.1, U9.5
NET_U9_8: R17.1, U9.8
NET_U11_1: R13.1, R14.1, U11.1
NET_U11_3: R15.2, R16.1, U11.3
NET_U11_4: R12.1, U11.4, U14.4, U15.2
NET_U12_1: R2.1, U12.1, U12.2
PROC_SPI1_MISO: U1.A7, U2.2
PROC_SPI1_MOSI: U1.C5, U2.5
PROC_SPI1_NSS: R7.1, U1.A9, U2.1
PROC_SPI1_SCK: U1.K4, U2.6
PROC_SYS_JTCK_SWCLK: U1.A10, U3.9
PROC_SYS_JTDO_TRACESWO: U1.A8, U3.13
PROC_SYS_JTMS_SWDIO: U1.A11, U3.7
PROC_TIM1_CH2: U1.D10, U16.2
PROC_TIM1_CH3: U1.C12, U16.3
PROC_USB_DM: U4.2, U5.3
PROC_USB_DP: U4.3, U5.2
RST_OUT_U3_SRESET_B: R9.1, U3.15, U14.1
VCC_S1_3V7: C17.1, C21.1, U8.4, U9.3, U9.4, U10.1
VCC_TIER1_2V5: C1.1, C2.1, C3.1, C4.1, C5.1, C6.1, C7.1, C8.1, C15.1, C16.1, C18.2, C19.1, C22.1, C23.1, F1.2, I1.2, R4.2, R6.2, R7.2, R8.2, R9.2, R11.2, R12.2, R13.2, R15.1, U1.C4, U1.E2, U1.G11, U1.G12, U1.H3, U2.8, U3.1, U11.6, U14.5, U15.5

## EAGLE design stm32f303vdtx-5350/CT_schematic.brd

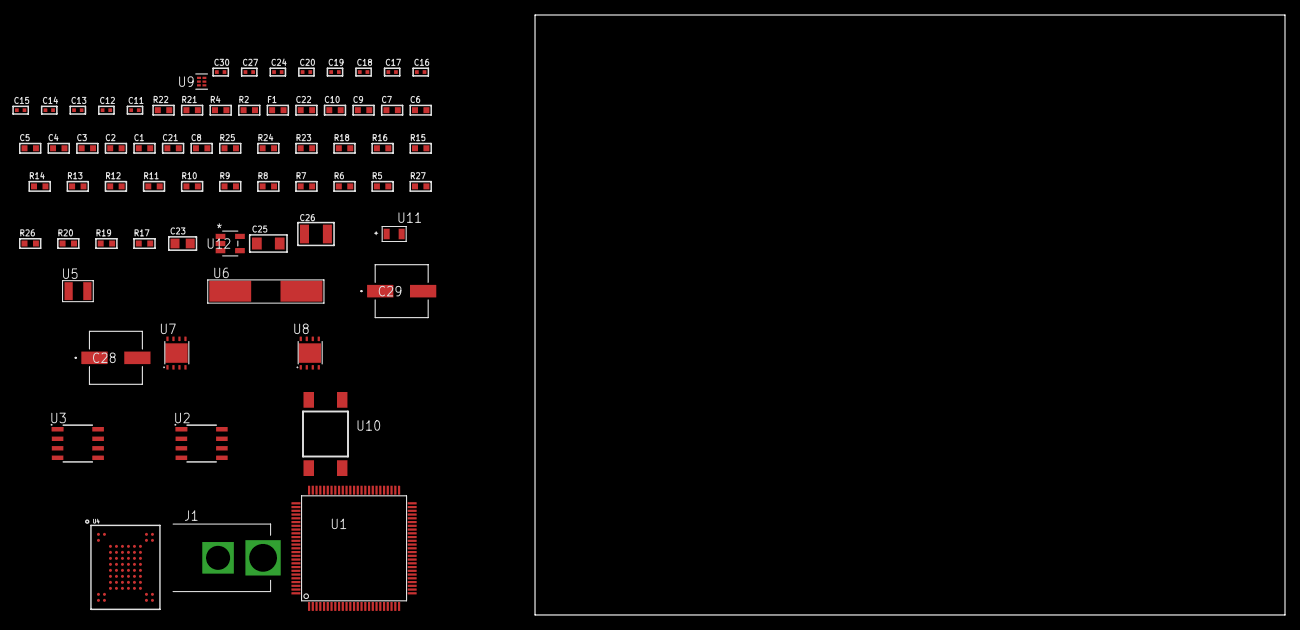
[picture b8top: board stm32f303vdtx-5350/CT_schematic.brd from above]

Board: 2 copper layers, 100.0 x 80.0 mm, 69 parts (0 on the bottom side), 38 nets, no tracks yet.

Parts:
C1, C10, C22: 1e-06; C0603
C2, C3, C4, C5, C6, C7: 1e-07; C0603
C8: 4.7e-06; C0603
C9: 1e-08; C0603
C11, C12, C13, C14: 1e-11; C0402
C15, C16, C24, C30: 1e-08; C0402
C17, C18, C19, C20, C27: 1e-07; C0402
C21: 2.2e-06; C0603
C23: 1e-05; C0805
C25: 1e-05; C1206
C26: 1e-05; C1210
C28, C29: 0.0001; EXV-9H
F1: 240.0; L0603
J1: PJ-037B; PJ-037B_PACKAGE
R2, R22: 1000.0; R0603
R4: 4700.0; R0603
R5, R6, R7, R8, R9, R10, R11, R12, R13, R14, R15, R16, R23, R24: 10000.0; R0603
R17, R19, R20: 100000.0; R0603
R18: 36000.0; R0603
R21: 1500.0; R0603
R25: 18000.0; R0603
R26: 470000.0; R0603
R27: 120000.0; R0603
U1: STM32F303VDT6; LQFP100
U2: AT25020B-SSHL-T; SOIC-8
U3: AT25160B-SSHL-T; SOIC-8
U4: mt29f4g08abbdah4; VFBGA-63
U5: ABS07-32.768KHZ-7-T
U6: ABLS-25.000MHZ-B2F-T
U7: LP2951ACSDX/NOPB; WSON-8
U8: LP3878SDX-ADJ/NOPB; WSON-8
U9: TPS3895ADRYR; SON-6
U10: 4-1437565-2; SW_4-1437565-2
U11: Q65110A2395; LGM67K-G1J2-24-Z
U12: nc7sz125m5x; NC7SZ125M5X

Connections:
CLK_CRYSTAL_U1_8: C11.1, U1.8, U5.1
CLK_CRYSTAL_U1_9: C12.1, U1.9, U5.2
CLK_CRYSTAL_U1_12: C13.1, U1.12, U6.1
CLK_CRYSTAL_U1_13: C14.1, U1.13, U6.2
GND: C1.2, C2.2, C3.2, C4.2, C5.2, C6.2, C7.2, C8.2, C9.2, C10.2, C11.2, C12.2, C13.2, C14.2, C15.2, C16.2, C17.2, C18.2, C19.2, C20.2, C21.2, C22.2, C23.2, C24.2, C25.2, C26.2, C27.2, C28.2, C29.2, C30.2, J1.2, R2.2, R5.2, R19.2, R22.2, R25.2, R27.2, U1.20, U1.27, U1.49, U1.74, U1.99, U2.4, U3.4, U4.C5, U4.F7, U4.K3, U4.K8, U7.3, U7.4, U7.PAD, U8.3, U8.PAD, U9.2, U11.C, U12.1, U12.3
NET_U1_14: R4.1, U1.14, U12.4
NET_U1_22: C9.1, C10.1, F1.1, U1.21, U1.22
NET_U1_94: R5.1, U1.94
NET_U1_98: U10.3, U10.4
NET_U2_3: R6.1, U2.3
NET_U2_7: R8.1, U2.7
NET_U3_3: R9.1, U3.3
NET_U3_7: R11.1, U3.7
NET_U4_C3: R16.1, U4.C3
NET_U4_C6: R13.1, U4.C6
NET_U4_C7: R14.1, U4.C7
NET_U4_C8: R12.1, U4.C8
NET_U4_D4: R15.1, U4.D4
NET_U7_5: R17.1, U7.5
NET_U7_7: R18.2, R19.1, U7.7
NET_U8_1: C24.1, U8.1
NET_U8_6: R21.2, R22.1, U8.6
NET_U8_8: R20.1, U8.8
NET_U9_1: R24.1, R25.1, U9.1
NET_U9_3: R26.2, R27.1, U9.3
NET_U9_4: R23.1, U9.4, U12.2
NET_U10_1: R2.1, U10.1, U10.2
PROC_SPI1_MISO: U1.31, U3.2
PROC_SPI1_MOSI: U1.32, U3.5
PROC_SPI1_NSS: R10.1, U1.29, U3.1
PROC_SPI1_SCK: U1.30, U3.6
PROC_SPI2_MISO: U1.53, U2.2
PROC_SPI2_MOSI: U1.54, U2.5
PROC_SPI2_NSS: R7.1, U1.51, U2.1
PROC_SPI2_SCK: U1.10, U2.6
VCC_S1_7V6: C22.1, C25.1, C28.1, C29.1, J1.1, R20.2, U7.8, U8.4
VCC_TIER1_1V8: C17.1, C18.1, C19.1, C20.1, C21.1, C23.1, C30.1, R12.2, R13.2, R14.2, R15.2, R16.2, R17.2, R18.1, U4.D3, U4.G4, U4.H8, U4.J6, U7.1, U12.5
VCC_TIER1_2V5: C1.1, C2.1, C3.1, C4.1, C5.1, C6.1, C7.1, C8.1, C15.1, C16.1, C26.1, C27.1, F1.2, R4.2, R6.2, R7.2, R8.2, R9.2, R10.2, R11.2, R21.1, R23.2, R24.2, R26.1, U1.6, U1.28, U1.50, U1.75, U1.100, U2.8, U3.8, U8.5, U9.6
